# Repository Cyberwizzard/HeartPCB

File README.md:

# HeartPCB - PCB with LEDs forming an illuminated and animated heart
Firmware and PCB layout for a heart shaped PCB with LEDs.

## About
I designed this PCB and the corresponding firmware as a wedding present for all guests attending. The PCB is the size and shape of a standard coaster, so that it could be used during the party by all guests to put their glass on top of it. When they go home they get a small plastic back containing the components to complete the kit.

The PCB has 18 LEDs, divided into 10 groups and is driven by a) an Arduino Pro Mini of b) statically lit by soldering some pads together.

## Option A
The simple build involves 8 x 47 Ohm and 2 x 150 Ohm resistors, a USB mini connector and 18 red 3mm LEDs.

Solder in place and solder the pads in the middle of the heart together. When plugged in, all LEDs will turn on.

## Option B
When using with an Arduino Pro Mini, there are a number of animations which are played. There are 2 buttons: the brightness button changes the brightness of all LEDs, the fast-forward button switches to the next animation. It supports a demo mode in which animations automatically cycle: hold down brightness until the animation is interrupted and the top-middle LED is on, keep pushing as more and more LEDs come on blinking. The more LEDs blink, the longer the animation is displayed before switching to the next. Set to 0 blinking LEDs to stop automatically forwarding.

The firmware saves the settings and state in the EEPROM (with write wear-levelling) every time the animation changes or the settings are changed.

The component list is 8 x 47 Ohm, 2 x 150 Ohm, 12 x 10k Ohm, USB mini connector, 18 red 3mm LEDs, 2 x 5x5mm push buttons, 1 x 470uF or 1000uF capacitor, 1 x Arduino Pro Mini (ATMEGA328 5V 16MHz)

### Troubleshooting
I had one board getting corrupted after the USB power bank feeding it got empty - my guess is EEPROM corruption. It got stuck loading some invalid stuff and the error LEDs kept turning on.
I fixed this by making error reporting optional and disabled (for production).

If the board does not start correctly due to EEPROM corruption, hold down any button while booting it.
It will now ignore the EEPROM and start the first animation. Press the fast-forward button to skip to the next animation and saving new settings to EEPROM.

## When using this project
Feel free to base your own gift off this design; drop me a note if you do as its nice to hear if this stuff is used again.

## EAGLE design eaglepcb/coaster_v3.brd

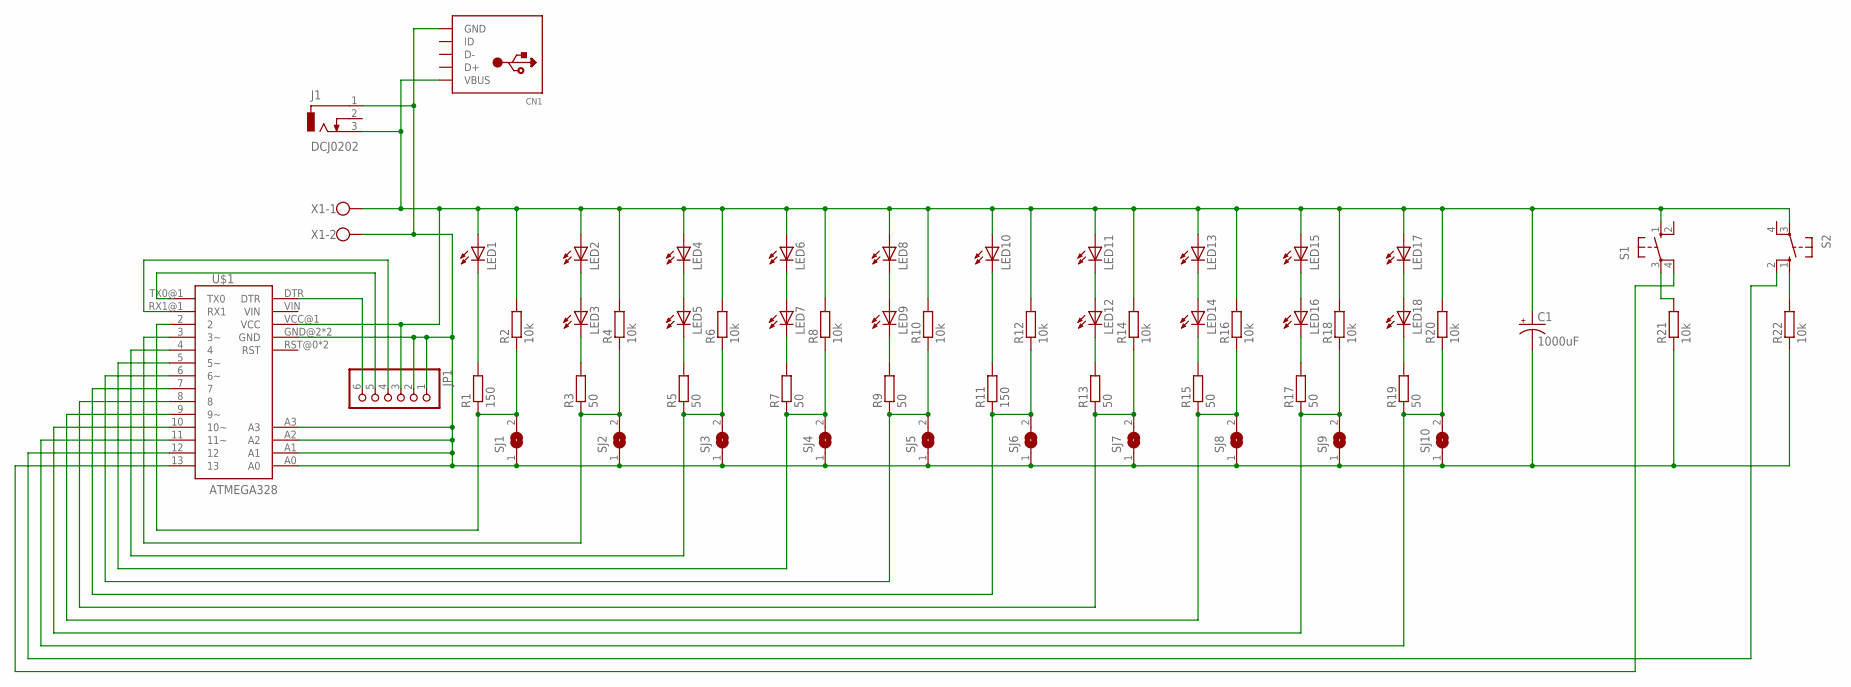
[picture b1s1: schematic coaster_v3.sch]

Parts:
C1: 1000uF; E3,5-8
CN1: USBTHM; USB-MINIB-THM
J1: DCJ0202
JP1: PINHD-1X6; 1X06
LED1, LED2, LED3, LED4, LED5, LED6, LED7, LED8, LED9, LED10, LED11, LED12, LED13, LED14, LED15, LED16, LED17, LED18: LED3MM
R1, R11: 150; 0207/7
R2, R4, R6, R8, R10, R12, R14, R16, R18, R20, R21, R22: 10k; 0207/7
R3, R5, R7, R9, R13, R15, R17, R19: 50; 0207/7
S1, S2: 10-XX; B3F-10XX
SJ1, SJ2, SJ3, SJ4, SJ5, SJ6, SJ7, SJ8, SJ9, SJ10: SJW
U$1: ATMEGA328; ATMEGA328-DX172858-LIGHT
X1: W237-102

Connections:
DTR: JP1.6, U$1.DTR
unnamed: LED1.K (C), R1.2
unnamed: LED10.K (C), R11.2
unnamed: R1.1, R2.1, SJ1.2, U$1.2
unnamed: LED2.K (C), LED3.A
unnamed: LED3.K (C), R3.2
unnamed: R3.1, R4.1, SJ2.2, U$1.3 (3~)
unnamed: LED4.K (C), LED5.A
unnamed: LED5.K (C), R5.2
unnamed: R5.1, R6.1, SJ3.2, U$1.4
unnamed: R21.2, S1.3
unnamed: LED6.K (C), LED7.A
unnamed: LED7.K (C), R7.2
unnamed: R7.1, R8.1, SJ4.2, U$1.5 (5~)
unnamed: LED8.K (C), LED9.A
unnamed: LED9.K (C), R9.2
unnamed: R9.1, R10.1, SJ5.2, U$1.6 (6~)
unnamed: S2.2 (S1), U$1.12
unnamed: R11.1, R12.1, SJ6.2, U$1.7
unnamed: LED11.K (C), LED12.A
unnamed: LED12.K (C), R13.2
unnamed: R13.1, R14.1, SJ7.2, U$1.8
unnamed: LED13.K (C), LED14.A
unnamed: LED14.K (C), R15.2
unnamed: R15.1, R16.1, SJ8.2, U$1.9 (9~)
unnamed: LED15.K (C), LED16.A
unnamed: LED16.K (C), R17.2
unnamed: R17.1, R18.1, SJ9.2, U$1.10 (10~)
unnamed: LED17.K (C), LED18.A
unnamed: LED18.K (C), R19.2
unnamed: R19.1, R20.1, SJ10.2, U$1.11 (11~)
unnamed: S1.4 (P1), U$1.13
unnamed: R22.2, S2.1 (S)
RXI: JP1.4, U$1.RX1@1 (RX1)
TXO: JP1.5, U$1.TX0@1 (TX0)
VCC_5V: C1.+, CN1.VBUS, J1.3, JP1.3, LED1.A, LED2.A, LED4.A, LED6.A, LED8.A, LED10.A, LED11.A, LED13.A, LED15.A, LED17.A, R2.2, R4.2, R6.2, R8.2, R10.2, R12.2, R14.2, R16.2, R18.2, R20.2, S1.1 (S), S2.3, U$1.VCC@1 (VCC), X1.1
VDD_GND: C1.-, CN1.GND, J1.1, JP1.1, JP1.2, R21.1, R22.1, SJ1.1, SJ2.1, SJ3.1, SJ4.1, SJ5.1, SJ6.1, SJ7.1, SJ8.1, SJ9.1, SJ10.1, U$1.A0, U$1.A1, U$1.A2, U$1.A3, U$1.GND@2 (GND), U$1.GND@3 (GND), X1.2

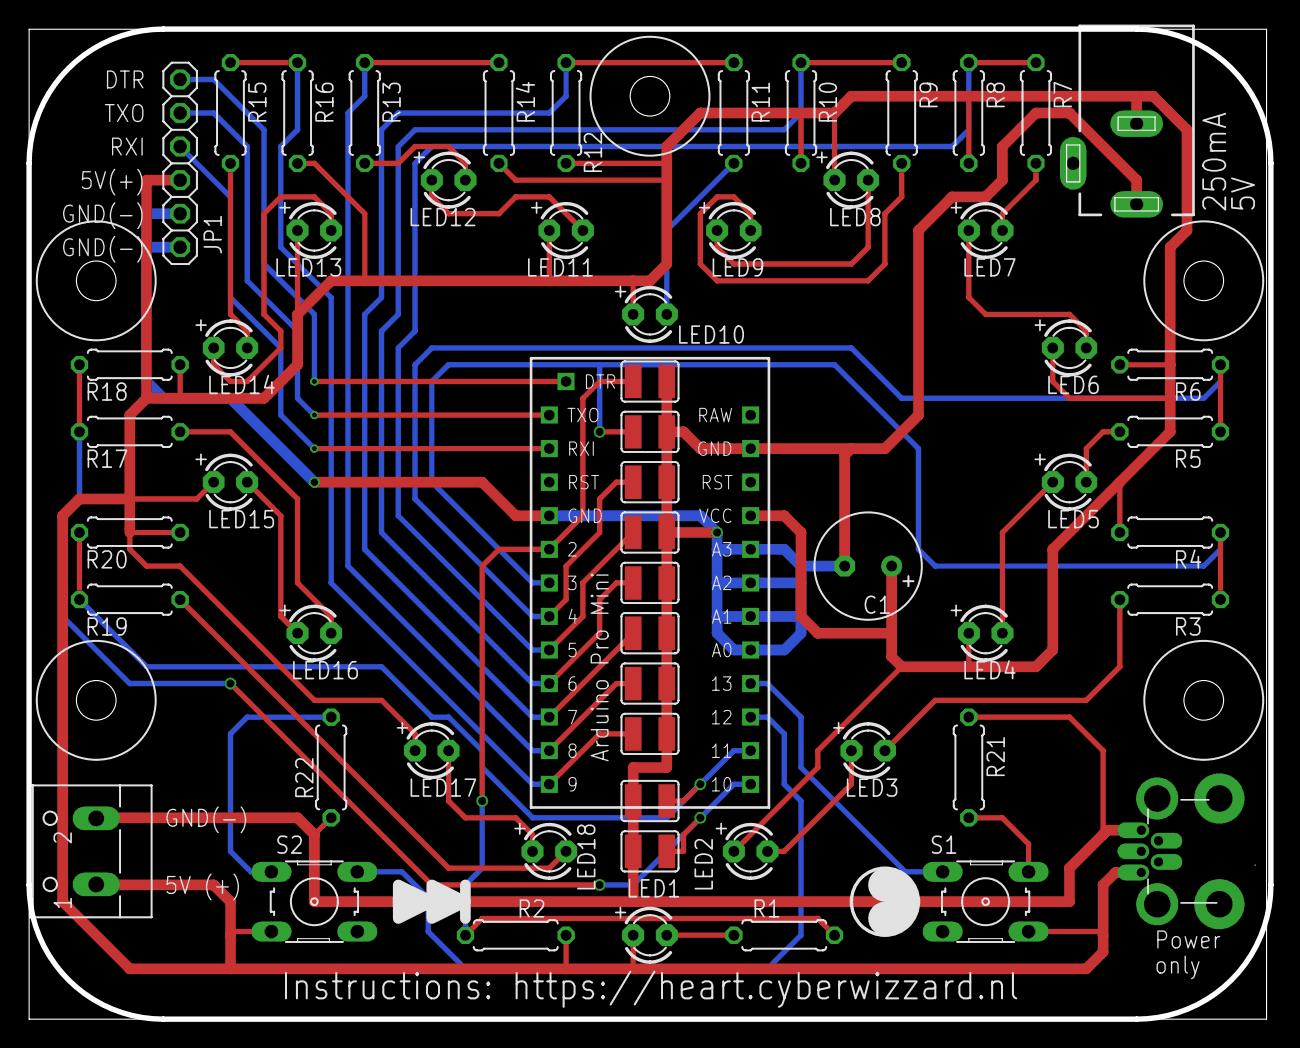
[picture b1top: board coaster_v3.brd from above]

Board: 2 copper layers, 94.0 x 74.9 mm, 58 parts (0 on the bottom side), 37 nets.

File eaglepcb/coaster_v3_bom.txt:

Partlist exported from D:/Users/Documents/eagle/heart_coaster/coaster_v3.sch at 4-5-2018 10:43

1  x 1000uF POLARIZED CAPACITOR
1  x USB CONNECTOR
1  x PIN HEADER 1X6
18 x LED RED 3MM
2  x RESISTOR 0207/7 150 OHMS
12 x RESISTOR 0207/7 10K OHMS
8  x RESISTOR 0207/7 47  OHMS
2  x MICROSWITCH 5MM
1  x ARDUINO PRO MINI (ATMEGA328)

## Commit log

2018-04-12 Initial snapshot of heart firmware
2018-04-12 Implemented nested interrupts, causes visual glitches
2018-04-13 Optimized ISR to less than 24us, fixed run-around animation
2018-04-13 Improved running around animation and split code into files
2018-04-13 Added support for tweaking the delay changes dynamically on the run-around animation
2018-04-16 Added drop-fill animation
2018-04-22 Added twinkle effect, implemented button handling, fixed various things
2018-07-20 Added EEPROM support, demo mode (auto-forward), added control for runtime demo control
2018-07-20 Production tweaks
2018-07-22 Error reporting optional and disabled, added EEPROM skip via button on boot
2018-07-22 Set theme jekyll-theme-cayman
2018-07-22 Added PCB source files
2018-07-22 Updated PCB files to v4
